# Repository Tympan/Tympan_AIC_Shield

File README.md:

# Tympan AIC Shield
## Add a CODEC to your Tympan with this daughter card!

This hardware design is in BETA and will be available for purchase March of 2019 at [Tympan.org](https://tympan.org/)

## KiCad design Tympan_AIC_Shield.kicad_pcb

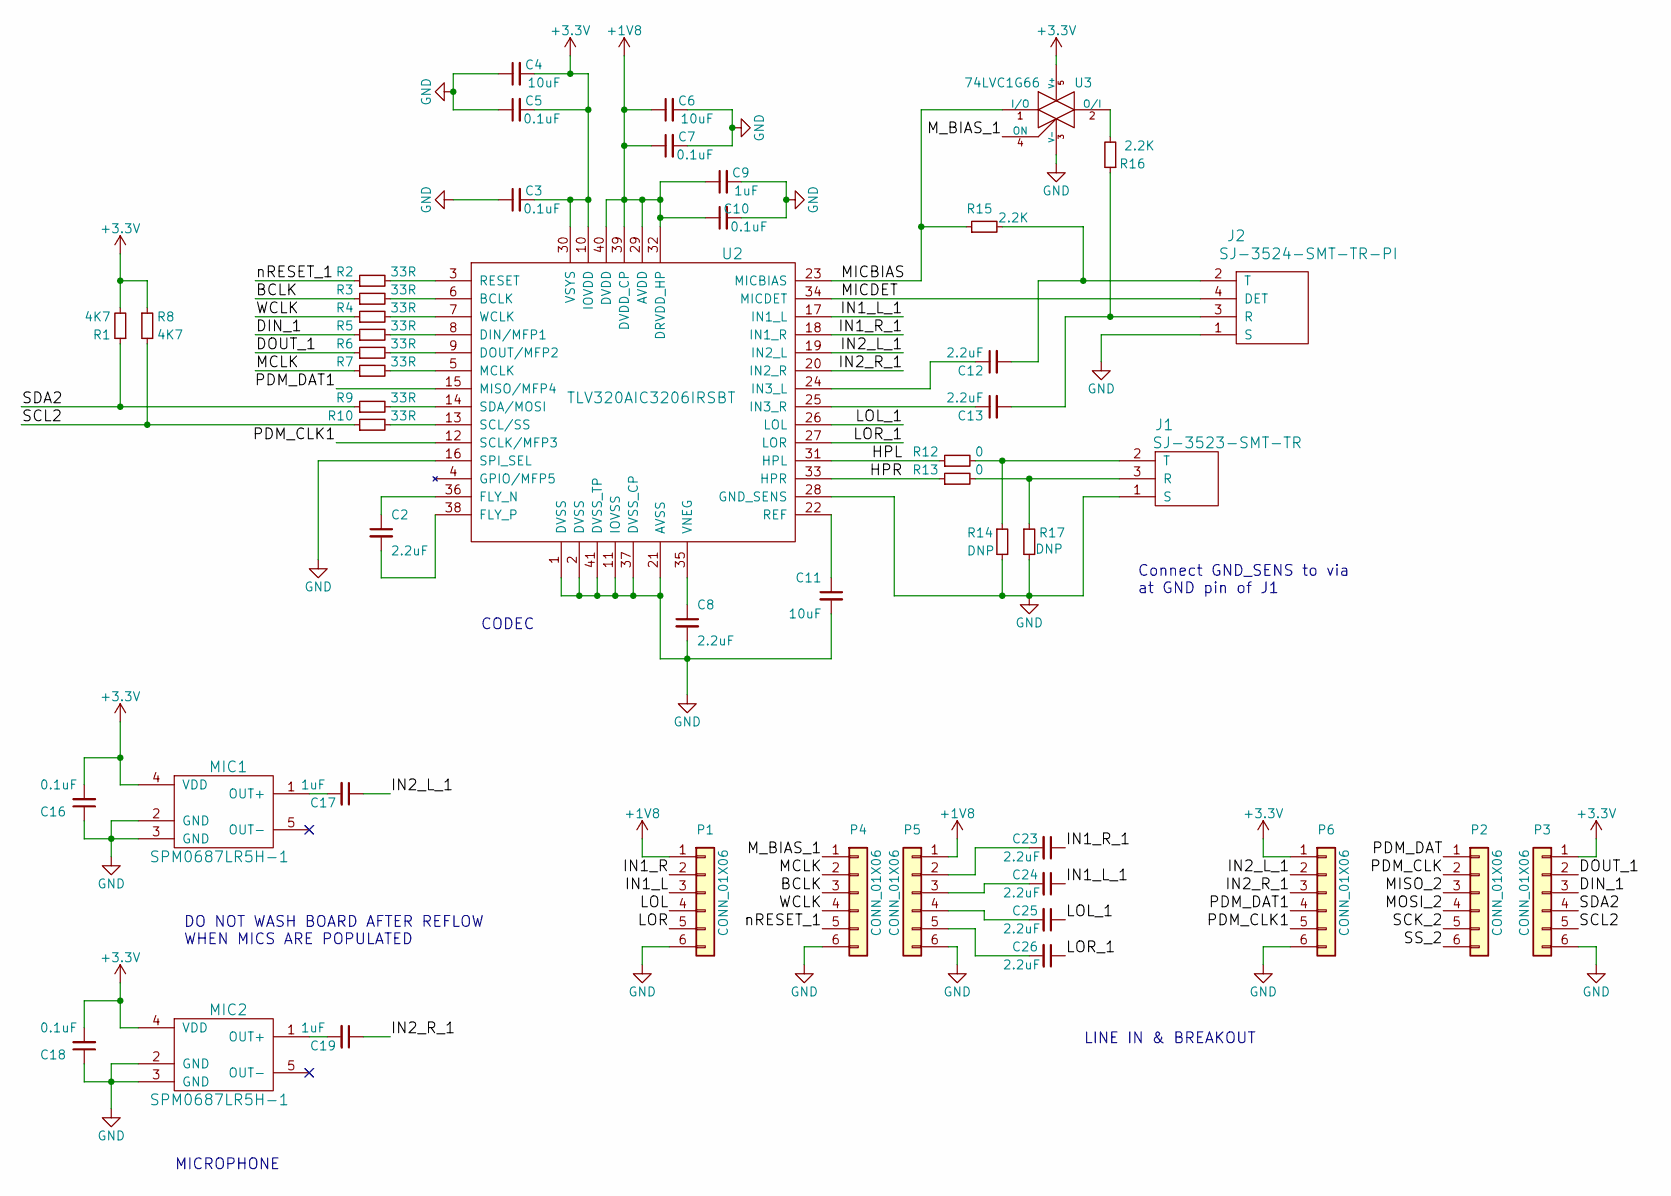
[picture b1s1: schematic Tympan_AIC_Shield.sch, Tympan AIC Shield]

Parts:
C2, C8, C12, C13, C23, C24, C25, C26: 2.2uF; C_0402
C3, C5, C7, C10, C16, C18: 0.1uF; C_0402
C4, C6, C11: 10uF; C_0402
C9, C17, C19: 1uF; C_0402
J1: SJ-3523-SMT-TR
J2: SJ-3524-SMT-TR-PI; SJ-3524-SMT-TR
MIC1, MIC2: SPM0687LR5H-1
P1, P2, P3, P4, P5, P6: CONN_01X06; Pin_Header_Straight_1x06_Pitch2.54mm
R1, R8: 4K7; R_0402
R2, R3, R4, R5, R6, R7, R9, R10: 33R; R_0402
R12, R13: 0; C_0603
R14, R17: DNP; C_0603
R15, R16: 2.2K; C_0603
U2: TLV320AIC3206IRSBT; UQFN-40-1EP_5x5mm_Pitch0.4mm
U3: 74LVC1G66; SOT-353_SC-70-5

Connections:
+1V8: C6.1, C7.1, C9.1, C10.1, P1.1, P5.1, U2.29 (AVDD), U2.32 (DRVDD_HP), U2.39 (DVDD_CP), U2.40 (DVDD)
+3V3: C3.2, C4.2, C5.2, C16.2, C18.2, MIC1.4 (VDD), MIC2.4 (VDD), P3.1, P6.1, R1.2, R8.1, U2.10 (IOVDD), U2.30 (VSYS), U3.5 (V+)
/BCLK: P4.3, R3.1
/DIN_1: P3.3, R5.1
/DOUT_1: P3.2, R6.1
/HPL: R12.1, U2.31 (HPL)
/HPR: R13.1, U2.33 (HPR)
/IN1_L: P1.3
/IN1_L_1: C24.1, U2.17 (IN1_L)
/IN1_R: P1.2
/IN1_R_1: C23.1, U2.18 (IN1_R)
/IN2_L_1: C17.1, P6.2, U2.19 (IN2_L)
/IN2_R_1: C19.1, P6.3, U2.20 (IN2_R)
/LOL: P1.4
/LOL_1: C25.1, U2.26 (LOL)
/LOR: P1.5
/LOR_1: C26.1, U2.27 (LOR)
/MCLK: P4.2, R7.1
/MICBIAS: R15.1, U2.23 (MICBIAS), U3.1 (I/O)
/MICDET: J2.4 (DET), U2.34 (MICDET)
/MISO_2: P2.3
/MOSI_2: P2.4
/M_BIAS_1: P4.1, U3.4 (ON)
/PDM_CLK: P2.2
/PDM_CLK1: P6.5, U2.12 (SCLK/MFP3)
/PDM_DAT: P2.1
/PDM_DAT1: P6.4, U2.15 (MISO/MFP4)
/SCK_2: P2.5
/SCL2: P3.5, R8.2, R10.1
/SDA2: P3.4, R1.1, R9.1
/SS_2: P2.6
/WCLK: P4.4, R4.1
/nRESET_1: P4.5, R2.1
GND: C3.1, C4.1, C5.1, C6.2, C7.2, C8.2, C9.2, C10.2, C11.2, C16.1, C18.1, J1.1 (S), J2.1 (S), MIC1.2 (GND), MIC1.3 (GND), MIC2.2 (GND), MIC2.3 (GND), P1.6, P3.6, P4.6, P5.6, P6.6, R14.2, R17.2, U2.1 (DVSS), U2.2 (DVSS), U2.11 (IOVSS), U2.16 (SPI_SEL), U2.21 (AVSS), U2.28 (GND_SENS), U2.37 (DVSS_CP), U2.41 (DVSS_TP), U3.3 (V-)
unnamed: C2.1, U2.36 (FLY_N)
unnamed: C2.2, U2.38 (FLY_P)
unnamed: C8.1, U2.35 (VNEG)
unnamed: C11.1, U2.22 (REF)
unnamed: C12.1, U2.24 (IN3_L)
unnamed: C12.2, J2.2 (T), R15.2
unnamed: C13.1, U2.25 (IN3_R)
unnamed: C13.2, J2.3 (R), R16.1
unnamed: C17.2, MIC1.1 (OUT+)
unnamed: C19.2, MIC2.1 (OUT+)
unnamed: C23.2, P5.2
unnamed: C24.2, P5.3
unnamed: C25.2, P5.4
unnamed: C26.2, P5.5
unnamed: J1.2 (T), R12.2, R14.1
unnamed: J1.3 (R), R13.2, R17.1
unnamed: R2.2, U2.3 (RESET)
unnamed: R3.2, U2.6 (BCLK)
unnamed: R4.2, U2.7 (WCLK)
unnamed: R5.2, U2.8 (DIN/MFP1)
unnamed: R6.2, U2.9 (DOUT/MFP2)
unnamed: R7.2, U2.5 (MCLK)
unnamed: R9.2, U2.14 (SDA/MOSI)
unnamed: R10.2, U2.13 (SCL/SS)
unnamed: R16.2, U3.2 (O/I)

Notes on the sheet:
MICROPHONE
CODEC
Connect GND_SENS to via at GND pin of J1
LINE IN & BREAKOUT
DO NOT WASH BOARD AFTER REFLOW WHEN MICS ARE POPULATED

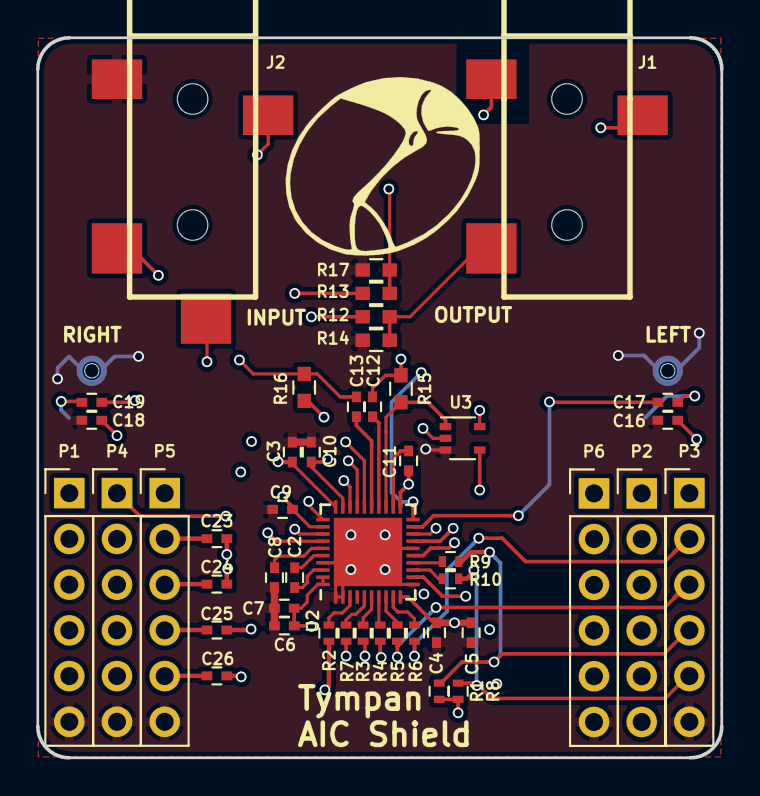
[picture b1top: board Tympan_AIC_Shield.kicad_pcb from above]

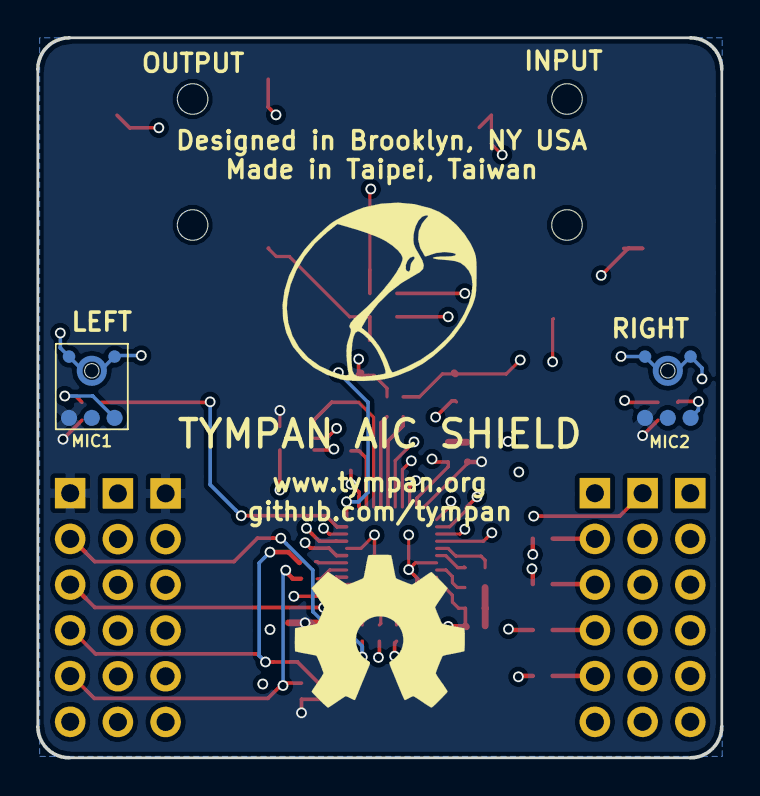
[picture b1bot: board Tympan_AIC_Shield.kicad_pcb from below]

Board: 4 copper layers, 38.0 x 40.0 mm, 48 parts (2 on the bottom side), 49 nets.

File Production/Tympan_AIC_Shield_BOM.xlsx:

Item | Reference | Package | Quantity | Value | Manufacturer | Part Number | Notes
1 | C23,C2,C8,C12,C13,C24,C25,C26 | C_0402 | 8 | 2.2uF | Murata | GRT155C71A225KE13D
2 | C3,C5,C7,C10,C16,C18 | C_0402 | 6 | 0.1uF | TDK Corporation | C1005X7R1H104K050BB
3 | C4,C6,C11 | C_0402 | 3 | 10uF | Murata | GRM155C80J106ME11J
4 | C9,C17,C19 | C_0402 | 3 | 1uF | Murata | GRM155C81C105KE15D
5 | J1 | SJ-3523-SMT-TR | 1 | Phone Out | CUI Inc | SJ-3523-SMT-TR
6 | J2 | SJ-3524-SMT-TR | 1 | Mic In | CUI Inc | SJ-3524-SMT-TR-PI
7 | MIC2,MIC1 | SPM0687LR5H-1 | 2 | DNP | DNP | DNP | DNP
8 | P5,P6 | Pin_Header_Straight_1x06_Pitch2.54mm | 2 | CONN_01X06 | Samtec | SSW-106-01-G-S
9 | P3,P4,P2,P1 | Pin_Header_Straight_1x06_Pitch2.54mm | 4 | CONN_01X06 | Samtec | SSW-106-03-T-S
10 | R1,R8 | R_0402 | 2 | 4K7 | Yageo | RC0603FR-074K7L
11 | R12,R13 | C_0603 | 2 | 0R | Vishay Dale | CRCW06030000Z0EA
12 | R14,R17 | C_0603 | 2 | DNP | DNP | DNP | DNP
13 | R15,R16 | C_0603 | 2 | 2.2K | Yageo | RC0603FR-072K2L
14 | R2,R3,R4,R5,R6,R7,R9,R10 | R_0402 | 8 | 33R | Yageo | RC0402FR-0733RL
15 | U2 | UQFN-40-1EP_5x5mm_Pitch0.4mm | 1 | CODEC | Texas Instrument | TLV320AIC3206IRSBT
16 | U3 | SOT-353_SC-70-5 | 1 | Analog Switch IC | Texas Instrument | TS5A3166DCKR

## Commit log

2019-03-07 Added I2C pullups, moved caps to front layer
    I2C needed pullup Rs
    Tied in to the 1V8 and GND on P1
    Moved caps to front layer for single sided load when not populating mics
2019-03-07 updated pdf
2019-03-18 Cleaned silk. Need to breakout PDM connections
2019-03-19 added PDM breakout
2019-03-19 gitignore
